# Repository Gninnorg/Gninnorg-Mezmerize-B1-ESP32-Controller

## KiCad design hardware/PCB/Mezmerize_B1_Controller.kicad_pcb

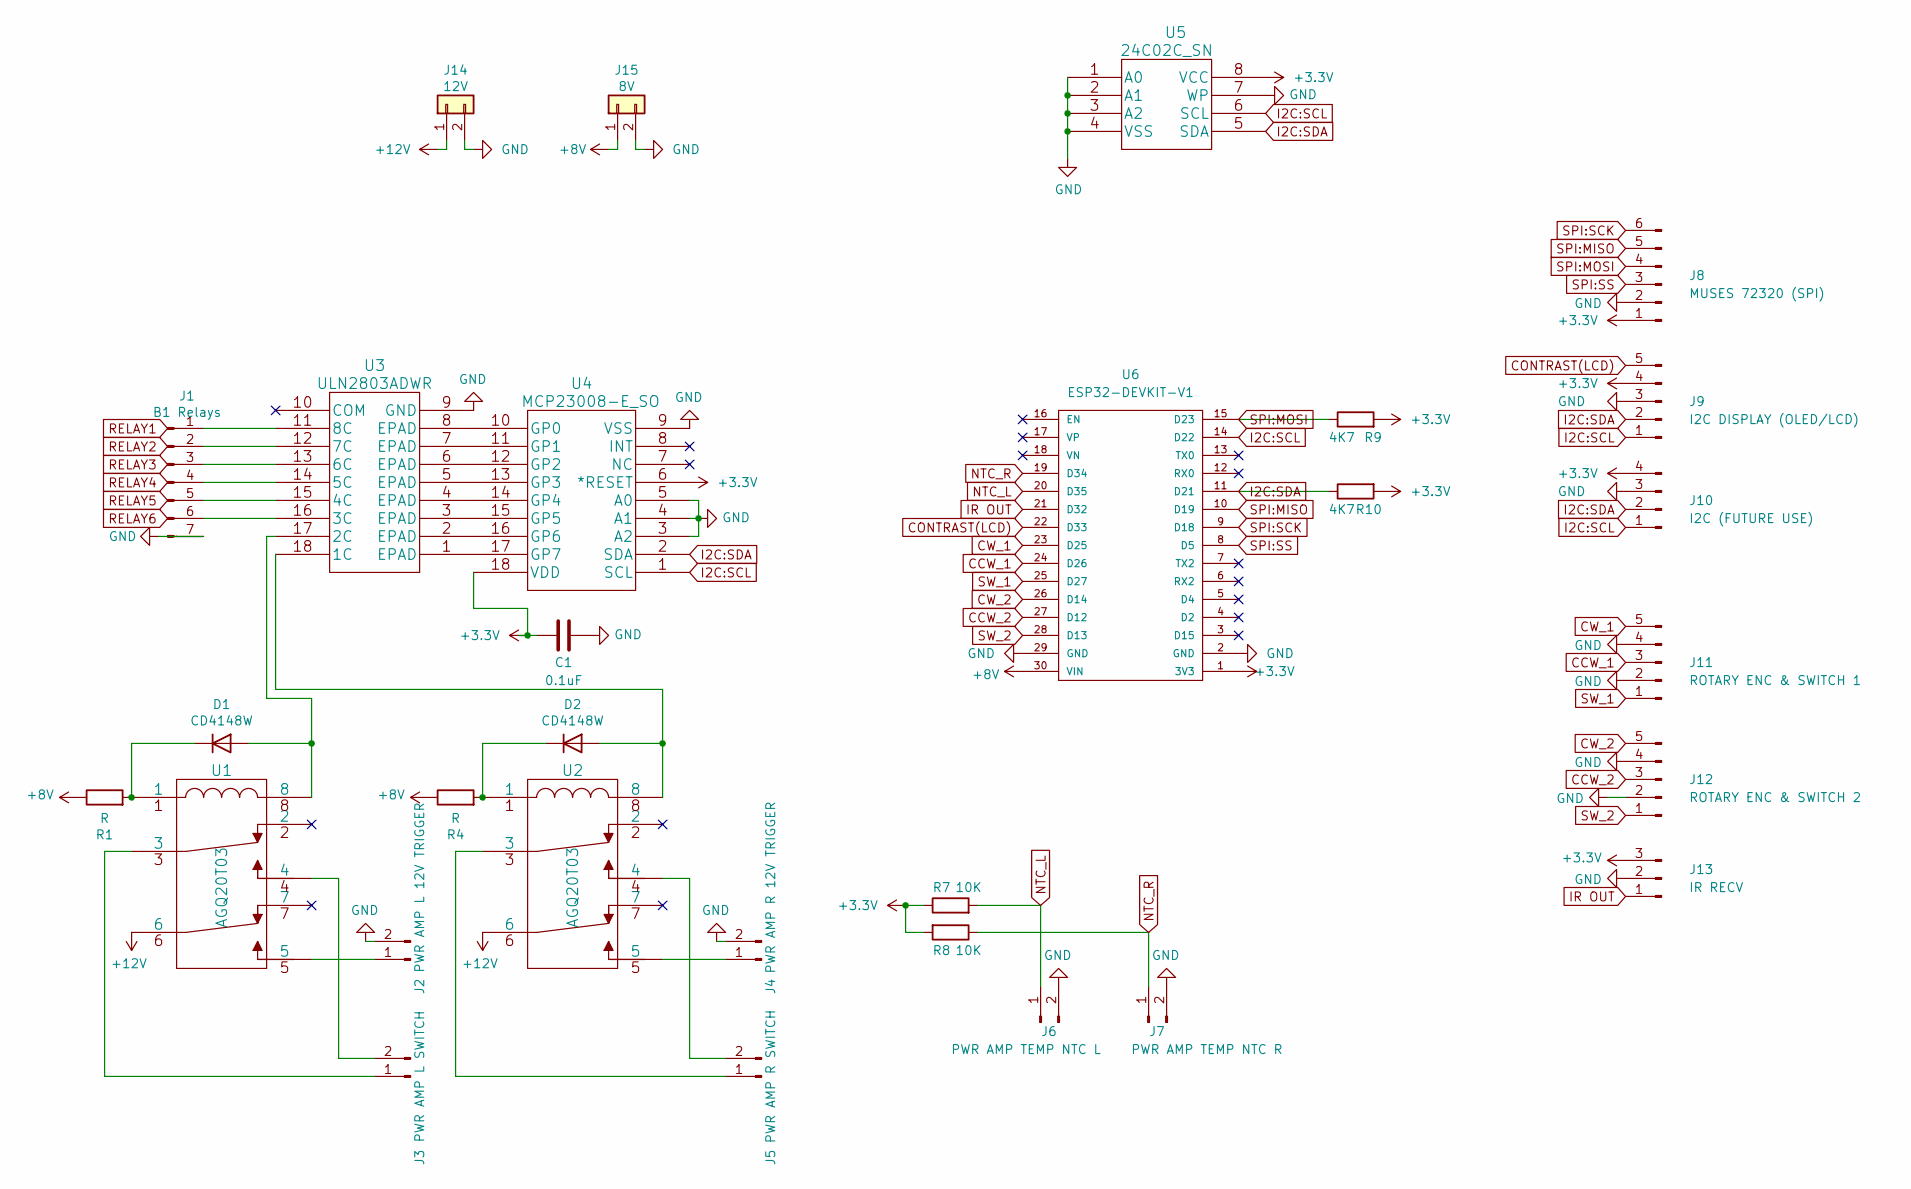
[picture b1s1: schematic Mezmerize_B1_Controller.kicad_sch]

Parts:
C1: 0.1uF; C_0805_2012Metric_Pad1.15x1.40mm_HandSolder
D1, D2: CD4148W; D_0805_2012Metric
J1: B1 Relays; JST_XH_B7B-XH-A_1x07_P2.50mm_Vertical
J2: PWR AMP L 12V TRIGGER; JST_XH_B2B-XH-A_1x02_P2.50mm_Vertical
J3: PWR AMP L SWITCH; JST_XH_B2B-XH-A_1x02_P2.50mm_Vertical
J4: PWR AMP R 12V TRIGGER; JST_XH_B2B-XH-A_1x02_P2.50mm_Vertical
J5: PWR AMP R SWITCH; JST_XH_B2B-XH-A_1x02_P2.50mm_Vertical
J6: PWR AMP TEMP NTC L; JST_XH_B2B-XH-A_1x02_P2.50mm_Vertical
J7: PWR AMP TEMP NTC R; JST_XH_B2B-XH-A_1x02_P2.50mm_Vertical
J8: MUSES 72320 (SPI); JST_XH_B6B-XH-A_1x06_P2.50mm_Vertical
J9: I2C DISPLAY (OLED/LCD); JST_XH_B5B-XH-A_1x05_P2.50mm_Vertical
J10: I2C (FUTURE USE); JST_XH_B4B-XH-A_1x04_P2.50mm_Vertical
J11: ROTARY ENC & SWITCH 1; JST_XH_B5B-XH-A_1x05_P2.50mm_Vertical
J12: ROTARY ENC & SWITCH 2; JST_XH_B5B-XH-A_1x05_P2.50mm_Vertical
J13: IR RECV; JST_XH_B3B-XH-A_1x03_P2.50mm_Vertical
J14: 12V; TerminalBlock_bornier-2_P5.08mm
J15: 8V; TerminalBlock_bornier-2_P5.08mm
R1, R4: R; R_Axial_DIN0207_L6.3mm_D2.5mm_P10.16mm_Horizontal
R7, R8: 10K; R_0805_2012Metric_Pad1.15x1.40mm_HandSolder
R9, R10: 4K7; R_0805_2012Metric_Pad1.15x1.40mm_HandSolder
U1, U2: AGQ20T03; AGQ20012
U3: ULN2803ADWR
U4: MCP23008-E_SO; MCP23008-E&slash_SO
U5: 24C02C_SN; SOIC-8-1EP_3.9x4.9mm_P1.27mm_EP2.41x3.3mm
U6: ESP32-DEVKIT-V1; MODULE_ESP32_DEVKIT_V1; PARTREV N/A

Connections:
+3V3: C1.1, J8.1, J9.4, J10.4, J13.3, R7.1, R8.2, R9.2, R10.2, U4.6 (*RESET), U4.18 (VDD), U5.8 (VCC), U6.1 (3V3)
+8V: J15.1, R1.1, R4.1, U6.30 (VIN)
+12V: J14.1, U1.6, U2.6
CCW_1: J11.3, U6.24 (D26)
CCW_2: J12.3, U6.27 (D12)
CONTRAST(LCD): J9.5, U6.22 (D33)
CW_1: J11.5, U6.23 (D25)
CW_2: J12.5, U6.26 (D14)
GND: C1.2, J1.7, J2.2, J4.2, J6.2, J7.2, J8.2, J9.3, J10.3, J11.2, J11.4, J12.2, J12.4, J13.2, J14.2, J15.2, U3.9 (GND), U4.3 (A2), U4.4 (A1), U4.5 (A0), U4.9 (VSS), U5.1 (A0), U5.2 (A1), U5.3 (A2), U5.4 (VSS), U5.7 (WP), U6.2 (GND), U6.29 (GND)
I2C:SCL: J9.1, J10.1, U4.1 (SCL), U5.6 (SCL), U6.14 (D22)
I2C:SDA: J9.2, J10.2, R10.1, U4.2 (SDA), U5.5 (SDA), U6.11 (D21)
IR OUT: J13.1, U6.21 (D32)
NTC_L: J6.1, R7.2, U6.20 (D35)
NTC_R: J7.1, R8.1, U6.19 (D34)
unnamed: D1.1 (K), R1.2, U1.1
unnamed: D1.2 (A), U1.8, U3.17 (2C)
unnamed: D2.1 (K), R4.2, U2.1
unnamed: D2.2 (A), U2.8, U3.18 (1C)
unnamed: J1.1, U3.11 (8C)
unnamed: J1.2, U3.12 (7C)
unnamed: J1.3, U3.13 (6C)
unnamed: J1.4, U3.14 (5C)
unnamed: J1.5, U3.15 (4C)
unnamed: J1.6, U3.16 (3C)
unnamed: J2.1, U1.5
unnamed: J3.1, U1.3
unnamed: J3.2, U1.4
unnamed: J4.1, U2.5
unnamed: J5.1, U2.3
unnamed: J5.2, U2.4
unnamed: U3.1 (EPAD), U4.17 (GP7)
unnamed: U3.2 (EPAD), U4.16 (GP6)
unnamed: U3.3 (EPAD), U4.15 (GP5)
unnamed: U3.4 (EPAD), U4.14 (GP4)
unnamed: U3.5 (EPAD), U4.13 (GP3)
unnamed: U3.6 (EPAD), U4.12 (GP2)
unnamed: U3.7 (EPAD), U4.11 (GP1)
unnamed: U3.8 (EPAD), U4.10 (GP0)
SPI:MISO: J8.5, U6.10 (D19)
SPI:MOSI: J8.4, R9.1, U6.15 (D23)
SPI:SCK: J8.6, U6.9 (D18)
SPI:SS: J8.3, U6.8 (D5)
SW_1: J11.1, U6.25 (D27)
SW_2: J12.1, U6.28 (D13)

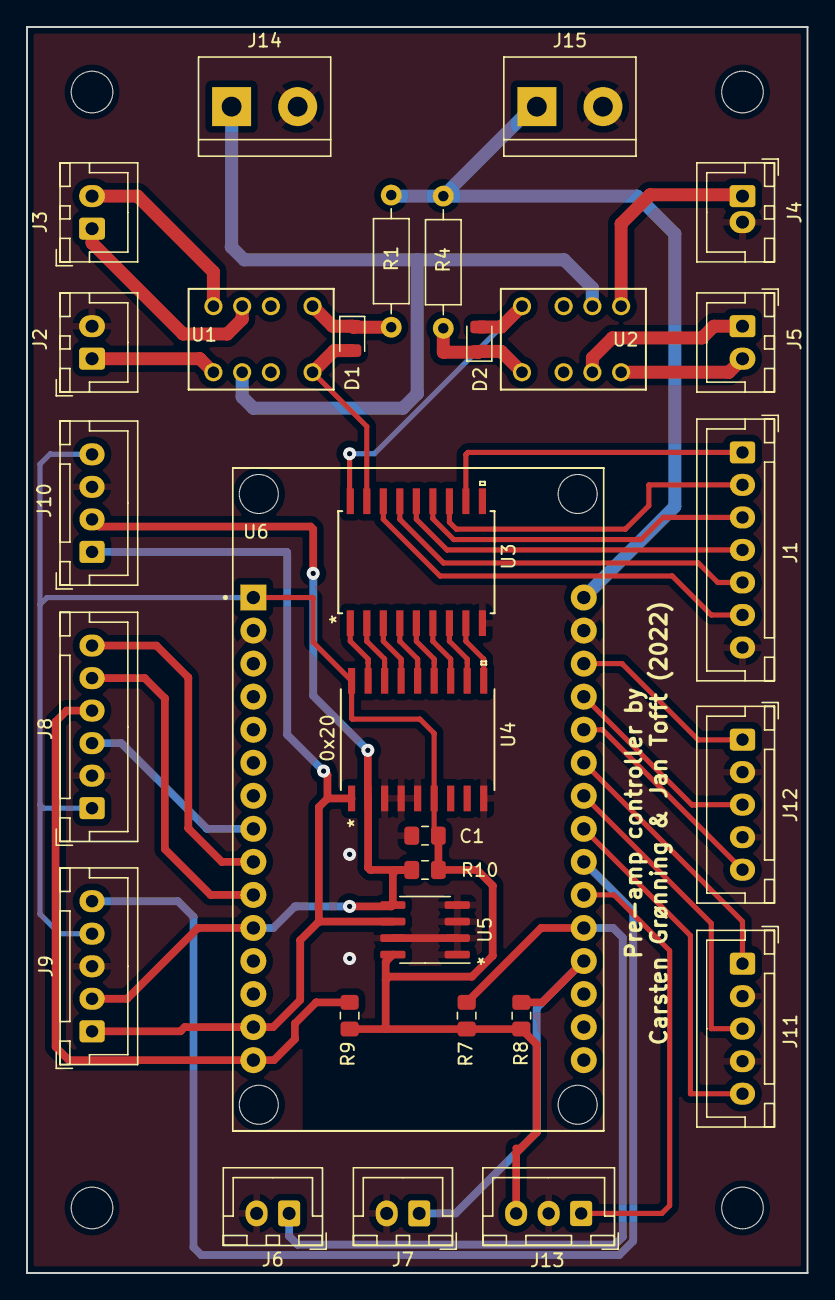
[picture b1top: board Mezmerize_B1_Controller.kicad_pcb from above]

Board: 2 copper layers, 60.0 x 95.8 mm, 30 parts (0 on the bottom side), 44 nets.

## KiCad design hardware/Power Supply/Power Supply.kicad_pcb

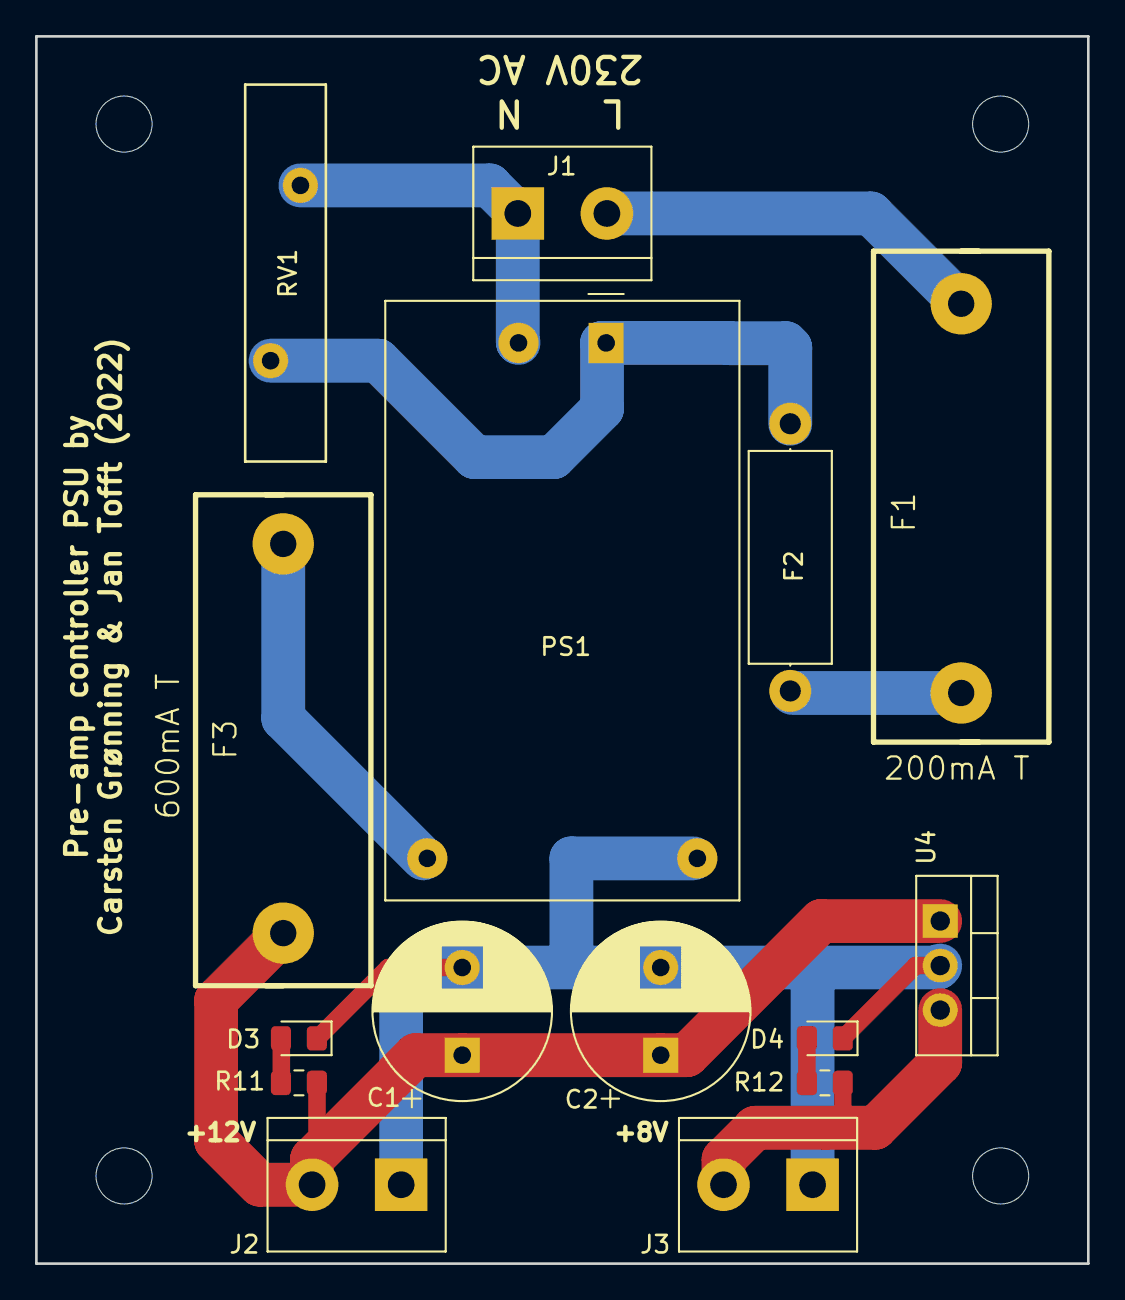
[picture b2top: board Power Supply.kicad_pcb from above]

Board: 2 copper layers, 60.0 x 70.0 mm, 15 parts (0 on the bottom side), 10 nets.

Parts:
C1, C2: 470uF; CP_Radial_D10.0mm_P5.00mm
D3, D4: LED; LED_0805_2012Metric_Pad1.15x1.40mm_HandSolder
F1: 200mA T; BLX-A
F2: Thermal fuse 73dgr; R_Axial_DIN0414_L11.9mm_D4.5mm_P15.24mm_Horizontal
F3: 600mA T; BLX-A
J1: 230 Vac; TerminalBlock_bornier-2_P5.08mm
J2: 12V; TerminalBlock_bornier-2_P5.08mm
J3: 8V; TerminalBlock_bornier-2_P5.08mm
PS1: HLK-PM12; Converter_ACDC_HiLink_HLK-PMxx
R11, R12: 4K7; R_0805_2012Metric_Pad1.15x1.40mm_HandSolder
RV1: Varistor; RV_Disc_D21.5mm_W4.6mm_P10mm
U4: L7808CV; TO-220-3_Vertical

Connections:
+8V: J3.2, R12.2, U4.3 (VO)
+12V: C1.1, C2.1, F3.1, J2.2, R11.2, U4.1 (VI)
GND: C1.2, C2.2, D3.1 (K), D4.1 (K), J2.1, J3.1, PS1.3 (-Vout), U4.2 (GND)
unnamed: D3.2 (A), R11.1
unnamed: D4.2 (A), R12.1
unnamed: F1.1, J1.2
unnamed: F1.2, F2.1
unnamed: F2.2, PS1.1 (AC/L), RV1.1
unnamed: F3.2, PS1.4 (+Vout)
unnamed: J1.1, PS1.2 (AC/N), RV1.2

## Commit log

2019-11-23 First merge with VxD
2019-11-23 Rename screen.ino
2019-11-23 Added IRLremote library
2019-11-23 merged screen.cpp into main.cpp
2019-11-23 A bit more cleanup
2019-11-23 Attempt to get source to compile
2019-11-24 added muses arduino library
2019-12-09 Add new empty library
2019-12-10 RelayController - First draft
2019-12-10 minor change to definitions
2019-12-11 added standard trigger functionality
2019-12-11 Changed comment
2019-12-11 Changes to RelayController
2019-12-11 test
2019-12-14 Added schematic, pcb-layout and 3D views of pcb to the folder "hardware"
2020-01-19 Clean up
2020-01-19 new main
2020-01-19 RelayController and Rotary Encoder
2020-01-20 Version 3 with JST-XH connectors
    Relay +/- corrected, fly back diodes added, two LEDs with resistors added to indicate +8V and +12V from PSU, pinheaders changed to JST-XH connectors
2020-01-21 changes to relay controller
2020-01-27 added IR and 2nd rotary encoder
2020-01-27 First draft of Build Guide
2020-01-28 Added photo of Mezmerize input relay connector
2020-01-28 Changes ports for rotary encoder 2
2020-02-02 Expanded main to switch all relays
2020-02-02 Added test of relays
2020-02-02 small changes
2020-02-02 gninnorg
2020-02-03 Added test of LDR circuit to measure if power amp is on or off
2020-02-03 Updated to reflect pcbs received 2020.01.31
2020-02-05 staged changes
2020-02-09 Clean up of RelayController and created function for temperature measurement
2020-02-09 Experiments with lcd display
2020-02-09 Show numbers with 4x4 chars
2020-02-12 Control relays from rotary encoder
2020-02-14 Changed to OLED again
2020-02-15 Works with OLED
2020-02-17 Lot of work to do yet, but we're getting closer
2020-02-18 Added function for temperature display
2020-02-18 Temperature checked every 30 seconds
2020-02-19 GUI and behaviour of menu changed
2020-02-20 Clean up in menu
2020-02-21 Refactor of menu ongoing
2020-02-21 Refactored and modularized editInputName() and added blinking cursor
2020-02-22 Added editNumericValue() for numeric menu settings
2020-02-22 Further settings in menu and eeprom read/write
2020-02-23 Menu is done - except for IR learning
2020-02-23 All settings in menu done - incl. IR learning
2020-02-23 Input names with upper and lower case
2020-02-29 Fix temp measurement and power loss handling
2020-03-01 Display of vol as 0-999 steps or -99.9-00.0 dB
2020-03-02 Fixed memory problem
2020-03-03 Rollback to avoid memory problems :-(
2020-03-04 Memory problem solved (again :-)
2020-03-05 Ready to implement volume and relay control
2020-03-05 SetVolume added
2020-03-06 Errors fixed - stable but issue with calc of att
2020-03-06 Vol debug info sent to Serial
2020-03-06 Changed default values
2020-03-07 optim calc. of vol profile in getattenuation()
2020-03-07 Almost no more TO DO's
2020-03-07 Smaller fixes after testing
2020-03-07 Further fixes and validation
2020-03-07 Trigger handling added
2020-03-07 Optimizations done
2020-03-08 Bug fix: Added check for received IR_PREVIOUS
2020-03-10 Added auto shutdown if temperature is too high
2020-05-27 Fixed volume att & input settings
2020-06-03 Fixed error infinite loop in input selection
2020-06-06 Fixed error when changing inputs
2020-06-08 Strangely this line solves the problem with double reads
2020-06-09 //Often the IR remote is to sensitive, reset reading if its to fast, but only if IR code is not REPEAT
2020-06-17 Fixed issue in relation to IR ONOFF
2020-06-21 Fix: select input on startup, mute at standby
2020-06-25 Fix: keep screen turned off during standby
2022-01-06 Update platformio.ini
    Change hardware platform to NodeMcu 32S
2022-01-13 Initial cleanup
2022-01-20 std:min()
2022-01-20 Compile ok
2022-01-20 added new libs
2022-01-20 change libraries IR & ENCODER
2022-02-02 Changed pin numbers to map to the ESP32 pins
2022-02-10 Display and Eeprom tested and working
2022-02-16 encoder
2022-02-18 Rotary almost working
2022-02-18 clickencoder lib fixes
2022-02-18 debug
2022-02-21 Minor problem fixes
2022-02-21 Removed use of PROGMEM
2022-02-21 And final traces of PROGMEM use removed
2022-02-21 Added BOM.xlsx
2022-02-23 All working as expected
2022-03-23 NTC updates
2022-03-30 schematic updated
2022-04-03 Schematic cleanup
2022-04-06 schenatics + symbols
2022-04-06 Update to new esp32 symbol
2022-04-10 removed local backups from git
2022-04-10 Don't send KiCad backup to git
2022-04-10 Last attempt .gitignore - now its working
2022-05-04 PCB split
2022-05-04 Split pcb
2022-05-18 psu pcb ready
2022-06-01 Missing changes ??
2022-06-01 mod psu + control v 0.25
2022-08-17 updated pcb
2022-08-24 Opdater print
2022-08-31 BOM created
2022-09-24 Updated footprint of eeprom to show orientation (leg 1)
2022-09-28 Changed union for eeprom and NTC resistance
2022-09-28 Changed NTC value and struct/union for eeprom data
2022-10-05 cleanup old code
2022-11-10 Removed SmartON from the code/menu
2022-11-12 added OTA and webserver
2022-11-12 smaller fixes
2022-11-18 added wifi setup with save to eprom
2022-11-20 Fixed min definition in .h file
2022-12-04 Created file
2022-12-04 Moved file
2022-12-17 Display when Wifi connection must be setup
2022-12-17 Cleanup display related code at startup
2022-12-27 Updated default settings (IR codes)
2023-02-05 Add control of power relay (D4)
2023-02-05 Changed input display and to do: triggers
2023-02-06 Power relay + wifi adjustments
2023-02-08 Change getTemperature
2023-02-09 Temperature update (precision adc)
2023-02-15 Fixed temp measurement + display temp
2023-02-18 Changed calibration + index.html
2023-02-19 changed index.html and processor()
2023-02-19 Datatype: getAttenuation from u_int8_t -> int16_t
2023-02-25 WebSocket WIP
2023-02-25 Set/show volume via Websocket interface
2023-02-25 Screensaver is turned off after Websocket command
2023-02-25 Fixed chrash when client connected (typo)
2023-02-26 Volume slider: max number of volume steps
2023-02-27 Web interface done (not pretty but works...)
2023-02-27 Webinterface works
2023-02-27 Fixed Power toggle from Websocket crashed Asyncftp
2023-02-28 Maintain ESP.restart after Wifi setup
2023-02-28 Typo
2023-03-01 Added calibration for Jan's ESP32
2023-03-01 Fixed display corruption (chng volume screensaver)
2023-03-01 Large cleanup setvolume, setinput & event handling
2023-03-05 New settings added (new version no.)
2023-03-06 add debug support
2023-03-06 add some comments
2023-03-12 Added datasheet of OLED display
2023-03-12 Bal.setting screen TO DO: setVolume to reflect it
2023-03-12 Implemented full solution for balance
2023-03-30 getAttenuation comments
2023-03-30 minor bug fixed in getAttenuation
2023-04-01 small fixes
2023-04-24 Additional websocket commands
2023-08-14 added support http input selec
